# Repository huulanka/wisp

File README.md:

# Wisp

Wisp is an open-source, self-hosted ESP32 room climate monitor. No cloud —
it publishes readings over MQTT into your own Home Assistant instance, which
exposes them to Apple HomeKit.

It tracks:

- **CO2** — SCD41
- **VOC / NOx (air quality)** — SGP41
- **Temperature & humidity** — SCD41, cross-checked against BME280
- **Barometric pressure** — BME280 (also compensates the SCD41's CO2 reading)
- **Ambient light** — BH1750

All hardware, firmware, and infrastructure needed to build and run one live
in this single repo.

## Repo structure

| Path | What's there | Status |
|---|---|---|
| [`/hardware`](hardware/) | KiCad project for the PCB — schematic, layout, Gerbers, BOM/CPL. ESP32-S3-WROOM-1 module, I2C sensors, USB-C only, 4-layer board. | Schematic and PCB routed, DRC clean, fab outputs exported. |
| `/firmware` | ESP-IDF firmware in Rust (`esp-idf-svc`), publishing sensor data over MQTT with OTA updates. | Not started. Design: [`docs/firmware-architecture.md`](docs/firmware-architecture.md). |
| `/infra` | Docker Compose: Mosquitto (MQTT, TLS, ACLs), a self-hosted OTA server, and Home Assistant bridging MQTT into HomeKit. | Not started. Design: [`docs/infra-architecture.md`](docs/infra-architecture.md). |
| [`/docs`](docs/) | Design concept, sensor rationale, expandability notes. | [`concept.md`](docs/concept.md), [`hardware-expandability.md`](docs/hardware-expandability.md). |

## Why these sensors

The SGP41 replaces the more common BME680: the BME680's gas reading only
becomes useful through Bosch's closed-source BSEC library, which doesn't sit
well with an MIT-licensed firmware. Sensirion's Gas Index Algorithm
(BSD-3-Clause) does the same job openly. Dropping the BME680 would also drop
barometric pressure, so the BME280 sits alongside the SGP41 for that —
and because the SCD41 needs ambient pressure to compensate its own CO2
reading, that pressure reading isn't a bonus, it feeds the primary
measurement.

Temperature and humidity are read from the SCD41; the BME280's readings are
kept as an independent cross-check rather than the source of truth, so
firmware can notice a failing sensor.

Full rationale: [`docs/concept.md`](docs/concept.md).

## MQTT topic structure

```
home/climate/<room>/{co2,temperature,humidity,voc,nox,pressure,lux}
```

First room: living room.

## Licensing

Each subfolder is licensed separately, matching its content type:

- [`/hardware`](hardware/LICENSE) → CERN-OHL-S v2
- `/firmware` → MIT
- `/docs` → CC-BY-4.0

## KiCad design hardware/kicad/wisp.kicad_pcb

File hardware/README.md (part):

# hardware

KiCad project for the Wisp board. See `/hardware/kicad` for schematic/PCB
source, `/hardware/scripts` for the generators that produce them, and
`/hardware/fab` for exported Gerbers/drill/BOM/CPL.

Board: **60 x 80 mm, 4 layers**, single-sided assembly (all parts on F.Cu).

## The design is generated, not hand-drawn

This is the most important thing to know before touching anything here.

| File | Role |
|---|---|
| `scripts/wisp_netlist.py` | **The design.** Every part, value, footprint, MPN and net. |
| `scripts/wisp_floorplan.py` | **The placement.** Fixed positions for the parts whose location is a decision; anchors for everything else. Also the board outline. |
| `scripts/gen_schematic.py` | builds `wisp.kicad_sch` |
| `scripts/gen_pcb.py` | builds `wisp.kicad_pcb`, in stages |

Edit the data, re-run the generators. **Do not hand-edit `wisp.kicad_sch`** —
it is overwritten. Rev A's schematic was produced by a throwaway script that
was never committed, which is why by Rev B nobody could reconstruct how it had
been built. That is the problem these two files exist to prevent.

```
python3 hardware/scripts/gen_schematic.py

KI=/Applications/KiCad/KiCad.app/Contents/Frameworks/Python.framework/Versions/Current/bin/python3
for s in strip outline build bond fill; do $KI hardware/scripts/gen_pcb.py $s; done
# ... route (see below) ...
for s in close join polish silk fill; do $KI hardware/scripts/gen_pcb.py $s; done
```

The PCB generator runs as **separate processes per stage on purpose**. pcbnew's
SWIG bindings stop resolving types for the rest of the interpreter once
anything has been `Remove()`d from the board — zones come back as raw
`SwigPyObject`, `GetTracks()` stops being iterable, `FootprintLoad()` breaks,
and some combinations segfault outright. Every stage therefore does its reads
first, its deletions last, and hands off through the file.

### Stages

| Stage | Does |
|---|---|
| `strip` | resets the antenna keepout and the zone outlines, then deletes all copper and footprints |
| `outline` | rewrites Edge.Cuts from `wisp_floorplan.OUTLINE` (plain text — it both deletes and creates) |
| `build` | places all 91 footprints and assigns every net from the schematic netlist |
| `bond` | gives each SMD power pad its own via to its plane, plus a GND stitching grid |
| `fill` | refills all five zones |
| `close` | deletes vias/tracks the router left dangling; run until it reports none |
| `join` | closes any connection the router left open, with a collision-checked A* |
| `polish` | widens anything below the 0.15mm minimum track width |
| `silk` | makes the silkscreen manufacturable (see below) |

## Validating the design

```
kicad-cli sch erc --severity-all --format json --output erc.json hardware/kicad/wisp.kicad_sch
kicad-cli pcb drc --severity-all --format json --output drc.json hardware/kicad/wisp.kicad_pcb
```

Run these against the project directory, not against a copy of
`wisp.kicad_pcb` somewhere else: `kicad-cli` only picks up
`wisp.kicad_dru` and `wisp.kicad_pro` by path, and the project file is where
the design rules live.

`gen_schematic.py` additionally refuses to emit anything unless every net
references a pin that exists, every footprint file resolves, and **every pin
of every part is claimed by exactly one net or explicitly listed in
`NO_CONNECT`**. That last check is what stops a forgotten pin from quietly
becoming an unrouted net three stages later.

## Stackup

| Layer | Use |
|---|---|
| **F.Cu** | components + signal routing, GND fill in the gaps |
| **In1.Cu** (`GND`) | **solid, uncut ground plane** |
| **In2.Cu** (`PWR`) | **solid +3V3 plane** |
| **B.Cu** | signal routing, GND fill in the gaps |

Nothing is ever routed on the two inner layers — they are planes only. The
Specctra DSN handed to the autorouter declares them `(type power)` so the
router cannot cut them; if you re-export the DSN, re-apply that patch, since
KiCad exports all four layers as `(type signal)` by default.

## Power distribution

Every **surface-mount** `+3V3`/`GND` pad gets its own short stub and via
straight down to the plane that owns that net, placed just off the pad by a
collision-checked search. Power connectivity never depends on a pour reaching
a pad. Rev A's long-running "unconnected pour island" findings were all that
failure mode; with a via per pad, a power pad can only be unconnected if its
via is missing, which DRC reports directly.

Two deliberate exceptions:

- **Plated through-hole pads are not bonded.** A PTH pad already spans
  F.Cu..B.Cu and meets its plane on the way through. Adding a via beside it
  buys nothing and puts a second drill 0.4mm from the first — that was the
  source of most hole-to-hole violations and of two dangling `+3V3` vias
  during the Rev B bring-up.
- **Large exposed pads get a via array inside the pad** (the SCD41's 4.8mm
  thermal pad, the module's 3.9mm one). A stub to a via outside them cannot
  even be searched for, because every candidate within 3mm of the pad centre
  is still on the pad. This is what a thermal pad wants anyway.

Both the via *and the stub track leading to it* are collision-checked.
Checking only the via lets the stub cut straight across whatever pad lies
between — 61 GND/+3V3 shorts on the first attempt.

## Floorplan

Placement is by function, not by arithmetic.

```
 y 0.0-7.5    antenna keepout, all four copper layers, x 8..52
 y 0.75-26.3  U3 ESP32-S3-WROOM-1, antenna flush with the top edge
 y 8-30       left: EN/IO0 support, reset+boot buttons, status LED
              right: J2/J3 headers on the right edge
 y 30-46      USB-C (left edge) -> U8 ESD -> F1 -> U2 buck -> L1
 y 43-48      test point grid, 4.0mm pitch
 y 48-62      left: small headers; right: J4/J9; buzzer
 y 62-80      sensor tab, milled free on three sides
```

Rules this enforces:

- **Decoupling sits next to the pin it serves.** `wisp_floorplan.ANCHOR` names
  the pad each passive belongs to and `gen_pcb.py` runs a collision-checked
  spiral search outward from it. The ESP32's 100nF and 10uF, the SCD41's
  100nF, and the SGP41's RC element all land within a few millimetres of their
  pin. Rev A had all of its decoupling on the *opposite* copper layer, 8-20mm
  away, where above a few MHz it does essentially nothing.
- **A part may not cross the milled slot to reach its pin.** The slot splits
  the board into exactly two regions, and the placer requires a part to land
  in the same one as its anchor pad. Without that check the SCD41's bulk
  capacitor was placed 10mm away with a slot in between.
- **Fixed placements are checked against each other.** Pin headers are
  anchored at pin 1, not at their centre, so a 1x08 header extends ~20mm
  *downwards* from its coordinate; spacing them by centre is how J5/J7 and
  J9/MH4 first ended up overlapping.
- **All 91 parts are on the front.** Single-sided assembly is cheaper, and it
  keeps the inner ground plane the only thing between the two routing layers.

## RF: antenna placement

`U3` sits at the top board edge with its antenna end pointing off-board, so
the required clearance is mostly free air rather than reserved board area. A
rule area over `x 8..52, y 0..7.5` forbids tracks, vias, pads and zone fill on
**all four copper layers**.

Rev A cleared only the module's own width (x 18..42), which left GND pour
flush with the antenna on both sides. This clears ~9mm either side. It stops
short of the board corners so the M3 mounting holes still have somewhere to
live — the keepout forbids pads, and a mounting hole is a pad.

### The module footprint is project-local, and why

`wisp:ESP32-S3-WROOM-1` is a copy of the stock KiCad footprint with two
changes:

1. **The courtyard is trimmed to the module body** (x -9.75..9.75,
   y -12.75..13.45). The stock courtyard is **48 x 41mm**: it applies
   Espressif's 15mm antenna clearance symmetrically around the whole module
   instead of only off the antenna end. Left alone it swallows a third of a
   60x80mm board, blocks every nearby placement, and produces
   courtyard-overlap DRC errors against parts nowhere near the module. Rev A
   hit exactly this with the WROOM-32.
2. **Its built-in antenna keepout zone is removed**, so the board carries one
   deliberate antenna rule area instead of two overlapping ones with different
   extents.

## Thermal isolation of the sensors

SCD41 (`U4`), SGP41 (`U5`), BH1750 (`U6`) and BME280 (`U7`) sit on a tab at
the bottom of the board, x 19.5-49, y 62-80, cut free by a 1.5mm milled slot
on three sides and joined to the main board through a 9mm neck. This is
Sensirion's and Bosch's own recommendation: without it the parts report PCB
temperature rather than room temperature, which for a room climate monitor
defeats the primary function.

The tab is larger than Rev A's 25 x 16.5mm. The SCD41 alone fills 40% of that,
leaving nowhere to put its own decoupling — which is exactly what went wrong
the first time. At 29.5 x 18mm every sensor keeps its decoupling on its own
side of the slot.

The SGP41 is placed at the far end of the tab from the SCD41: it runs a
hotplate, and the SCD41 is the sensor whose temperature reading has to stay
honest.

**Known tradeoff, deliberate:** the GND and +3V3 planes still run through the
neck, so the isolation comes from slot geometry and distance rather than from
a copper break. Narrowing the planes at the neck would improve it further and
remains a reasonable future refinement.

## Routing

Signals are routed with Freerouting (headless, `--gui.enabled=false -mt 1`;
multi-threaded optimisation is flagged by Freerouting itself as producing
clearance violations). The DSN is exported with `pcbnew.ExportSpecctraDSN` —
note that `kicad-cli pcb export` has no `specctra-dsn` subcommand — then
patched so the inner layers are `(type power)`.

Afterwards, `close` removes anything the router left dangling and `join`
closes any remaining open connection with a collision-checked A* over
F.Cu/B.Cu with via transitions. `join` reads the DRC report to find what is
open and rasterises the **whole** target net as its goal; aiming at a single
reported coordinate is fragile, because a track's `GetPosition()` is one end
of it rather than the nearest point.

**Minimum track width is 0.15mm.** The escapes under the fine-pitch sensors
genuinely need it, and it is comfortably inside JLCPCB's 4-layer capability
(0.127mm). Rev A instead routed at 0.25mm clearance and widened the router's
0.15mm stubs back to 0.20mm afterwards; doing that here created clearance
violations against neighbouring pads, and re-routing at 0.25mm made the router
thrash without converging.

**If a net comes back unroutable, look at the test points first.** They sit in
the busiest part of the board, and at Rev A's 3.2mm pitch the router boxed one
in completely — a net that no amount of post-processing can reach, because the
pad has no escape lane in any direction. They are at 4.0mm pitch now.

### J1 (USB-C)

The receptacle brings D+ out on pads A6/B6 and D- on A7/B7, interleaved down
the column as **B6, A7, A6, B7** at 0.5mm pitch, so connecting each pair needs
exactly one layer crossing and a 0.6mm via needs ~1.2mm of vertical room. On
Rev A this required a hand-placed fanout before autorouting.

On Rev B the pair runs J1 -> U8 (USBLC6 ESD array) -> U3 rather than J1 -> a
UART bridge, and U8 is placed to give the crossing room, so the autorouter
solves it unaided. If you re-place J1 or U8 and D- comes back unroutable, this
is why.

## Silkscreen

At 91 parts on 60x80mm a footprint's own silk outline routinely lands on the
neighbouring part's pads. The `silk` stage:

- moves every footprint silk **graphic** to F.Fab, where it still appears in
  the assembly drawing;
- **auto-places the reference designators** with a collision-checked search
  against pads, board edge and each other, largest parts first, and demotes
  only the ones with nowhere to go;
- moves **Value** to F.Fab;
- and hides the custom metadata fields.

That last one matters more than it sounds. `MPN`, `Manufacturer`, `Rating` and
`LCSC` are created on **F.SilkS by default and parked at the footprint
origin**, stacked on top of each other and on the pads — 422 text items nobody
ever intended to print. They are not returned by `GraphicalItems()`, so they
are invisible to every other pass, and they were the entire source of ~440
silkscreen DRC violations. If silkscreen violations reappear after adding a
field, this is the first place to look.

## Known ERC warnings (accepted, not bugs)

**`Pins of type Bidirectional and Power output are connected`** (U7 pin 5 /
SDO tied to GND)

`U7` (BME280) pin 5 (SDO) is intentionally strapped to GND to select I2C
address `0x76`. The symbol marks SDO `Bidirectional`, so ERC flags any
bidirectional pin wired to a power net. Either address strap produces this;
it cannot be avoided while the address is fixed in hardware.

Rev A's two `lib_symbol_mismatch` warnings are gone: the generator embeds
symbols straight from the installed library, so a cached copy cannot drift
from it.

## Known DRC findings

None. `kicad-cli pcb drc --severity-all` is clean: 0 violations, 0 unconnected
items, 0 schematic-parity errors.

This is no longer a low bar: `wisp.kicad_dru` used to carry no rules, and the
board's own `min_silk_clearance` / `solder_mask_to_copper_clearance` were both
0mm, so KiCad's DRC could not have caught a real fab-capability problem even
if one existed. A JLCPCB DFM report against an earlier build of this board
found real ones — 0.15mm silk-line width flagged, silkscreen text on top of
vias, negative silk/pad clearance — none of which local DRC saw, because
nothing was checking for it. Design rules in `wisp.kicad_pro` now match
JLCPCB's published capability (`min_silk_clearance` 0.15mm,
`solder_mask_to_copper_clearance` 0.1mm, `min_hole_clearance` 0.3mm) instead
of the KiCad defaults, and DRC is clean against those.

The root cause of the silkscreen findings was in `gen_pcb.py`'s `silk` stage,
not just the missing rule: reference-designator placement estimated each
label's width from a `0.62mm/character` formula instead of asking KiCad for
the real rendered bounding box, and undershot it by up to 0.48mm — enough
that designators the search believed were clear were actually touching
neighbouring pads and vias. It also never considered vias as obstacles at
all. Both are fixed: the search now queries `GetBoundingBox()` on the actual
text object, and vias are indexed alongside pads.

Three design rules were deliberately changed from Rev A/B, all recorded in
`wisp.kicad_pro`:

- `min_track_width` 0.20 -> **0.15mm** — see Routing above.
- `min_resolved_spokes` 2 -> **1** — a handful of GND pads can only get one
  thermal spoke past their neighbours. One spoke is a valid connection, and
  every affected pad is a power pad that also carries its own plane via, so
  the spoke is a secondary path in any case.
- `min_hole_clearance` 0.25 -> **0.3mm** — JLCPCB's stated absolute minimum is
  0.28mm; 0.25 was below it even though nothing on the board was actually
  that tight.

Two things the DFM report flags that are **not** being changed, both reviewed
and accepted rather than silently ignored:

- **Every via's annular ring is 0.15mm** (0.6mm pad / 0.3mm drill), which
  JLCPCB's own DFM tool marks as a Warning because it sits exactly at their
  stated *absolute minimum* rather than their *recommended* 0.20mm. Widening
  every via on this already-dense 60x80mm/91-part board would mean re-routing
  under a tighter budget for a purely precautionary margin; treated the same
  way as the `min_track_width` and `min_resolved_spokes` exceptions above.
- **J1's four shield-ground pads are 0.6mm oval plated slots**, flagged by
  JLCPCB as a slot-width Danger. This geometry comes from KiCad's own stock
  `Connector_USB:USB_C_Receptacle_HRO_TYPE-C-31-M-12` footprint (the part
  actually specified: HRO TYPE-C-31-M-12, LCSC C165948), not from anything
  wisp-specific, and the same footprint is in wide use on JLCPCB-fabricated
  boards. Not changed here since fixing it means swapping the connector
  itself; worth a manual check with JLCPCB before ordering if it matters for
  your run.

## Fab outputs

`hardware/fab/gerbers/` contains only the layers a fab actually needs — the
four copper layers, paste, silkscreen, mask and the board profile, plus
separate PTH/NPTH Excellon drill files and their maps.

Check `wisp-job.gbrjob` after any re-export: it must report `LayerNumber: 4`
with `Copper,L1,Top` / `Copper,L2,Inr` / `Copper,L3,Inr` / `Copper,L4,Bot`.
That file, not the filename extension, is what states the stackup order.

## Before ordering

**`wisp:BH1750FVI-TR_WSOF6` is now verified.** ROHM's mechanical drawing
(BH1750FVI Technical Note No.11046EDT01 Rev.D, p.14 "Package Outlines") turned
out to be reachable after all; the land pattern was rebuilt from its figures
(body 1.6 x 2.6mm, 0.5mm pitch, 0.22mm lead width, 0.27mm lead foot) and
cross-checked against the LCSC C78960 listing's own generated footprint,
which agrees on pitch and pad size once its axes are rotated into this
footprint's convention. Pin 7 is the exposed centre pad; the datasheet (p.16,
"Cautions on use" #10) says explicitly not to solder or electrically connect
it, so it is copper-only with no paste and no net, for mechanical registration
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
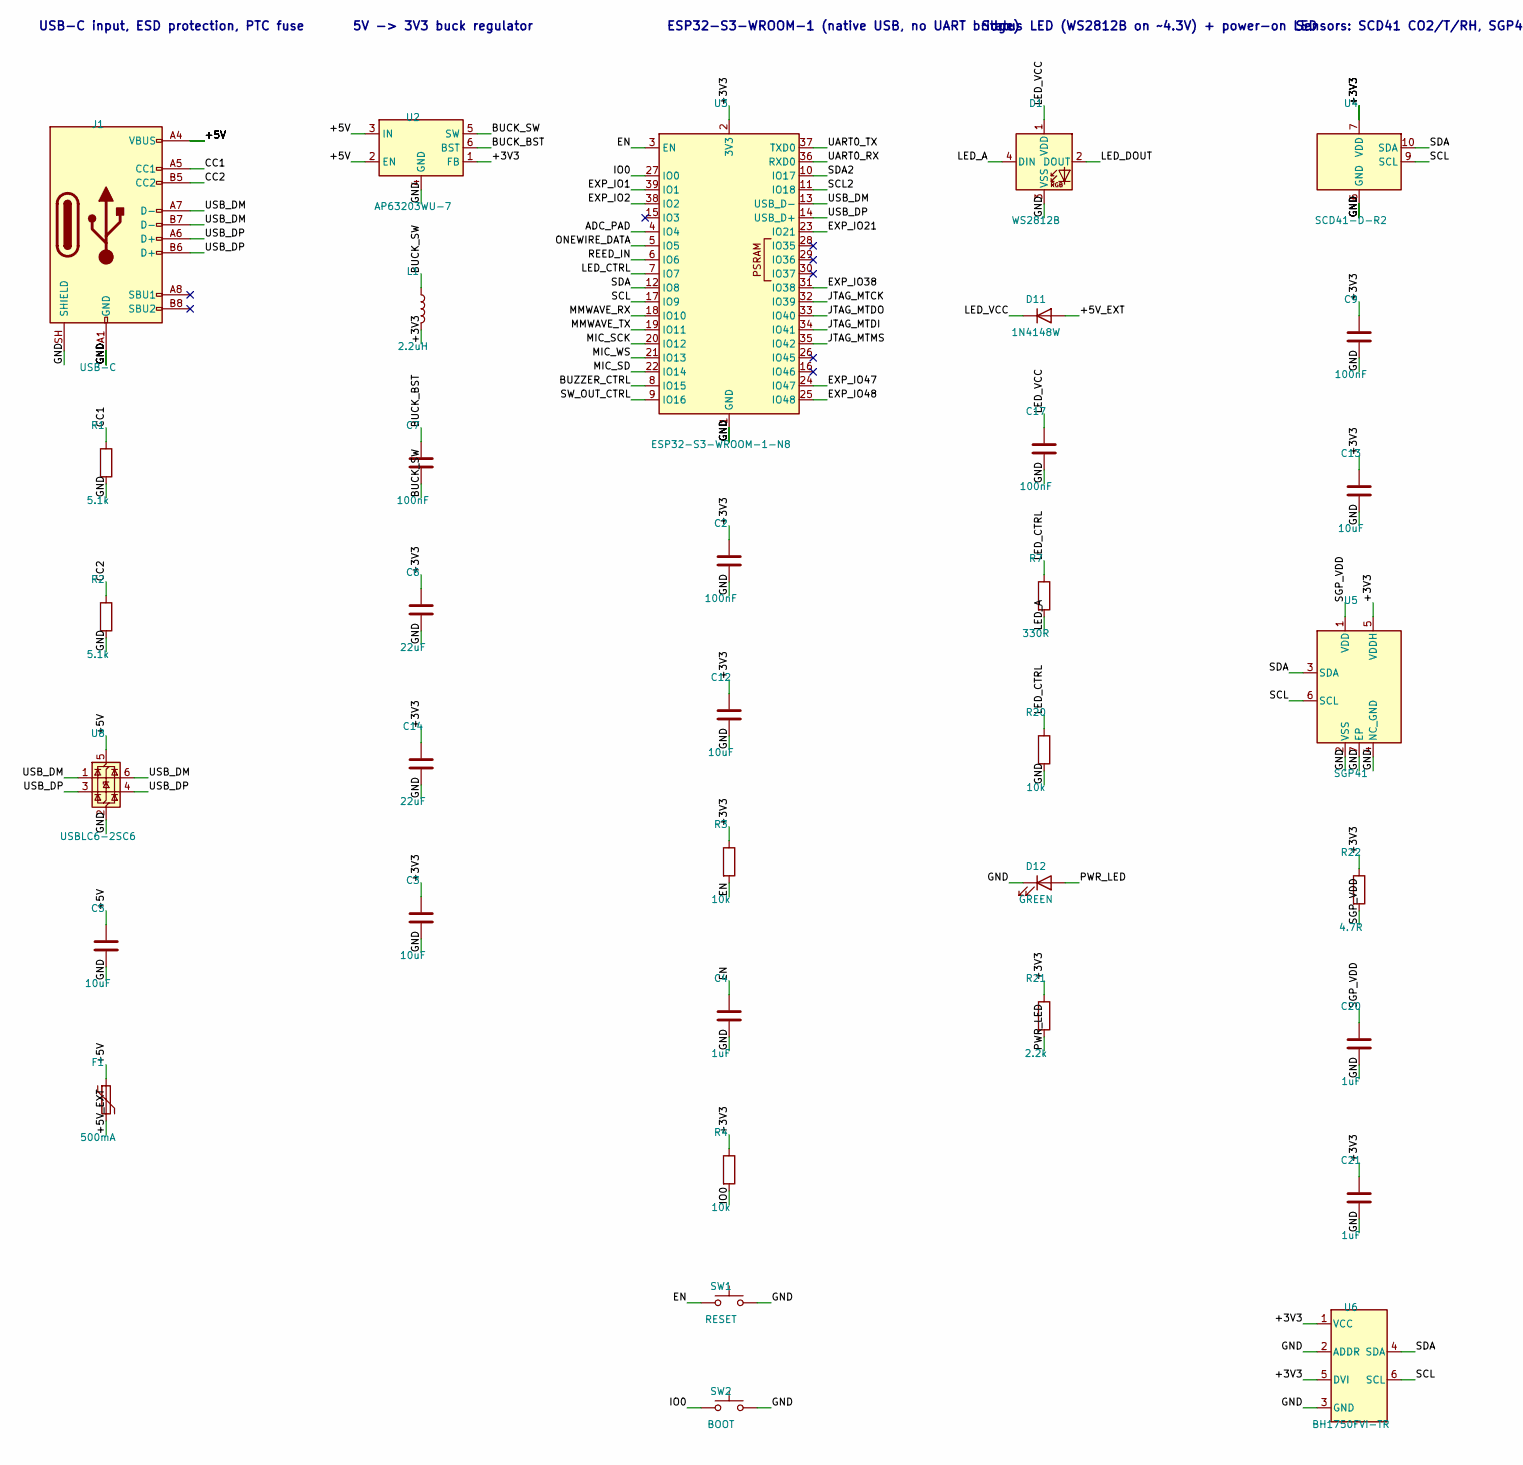
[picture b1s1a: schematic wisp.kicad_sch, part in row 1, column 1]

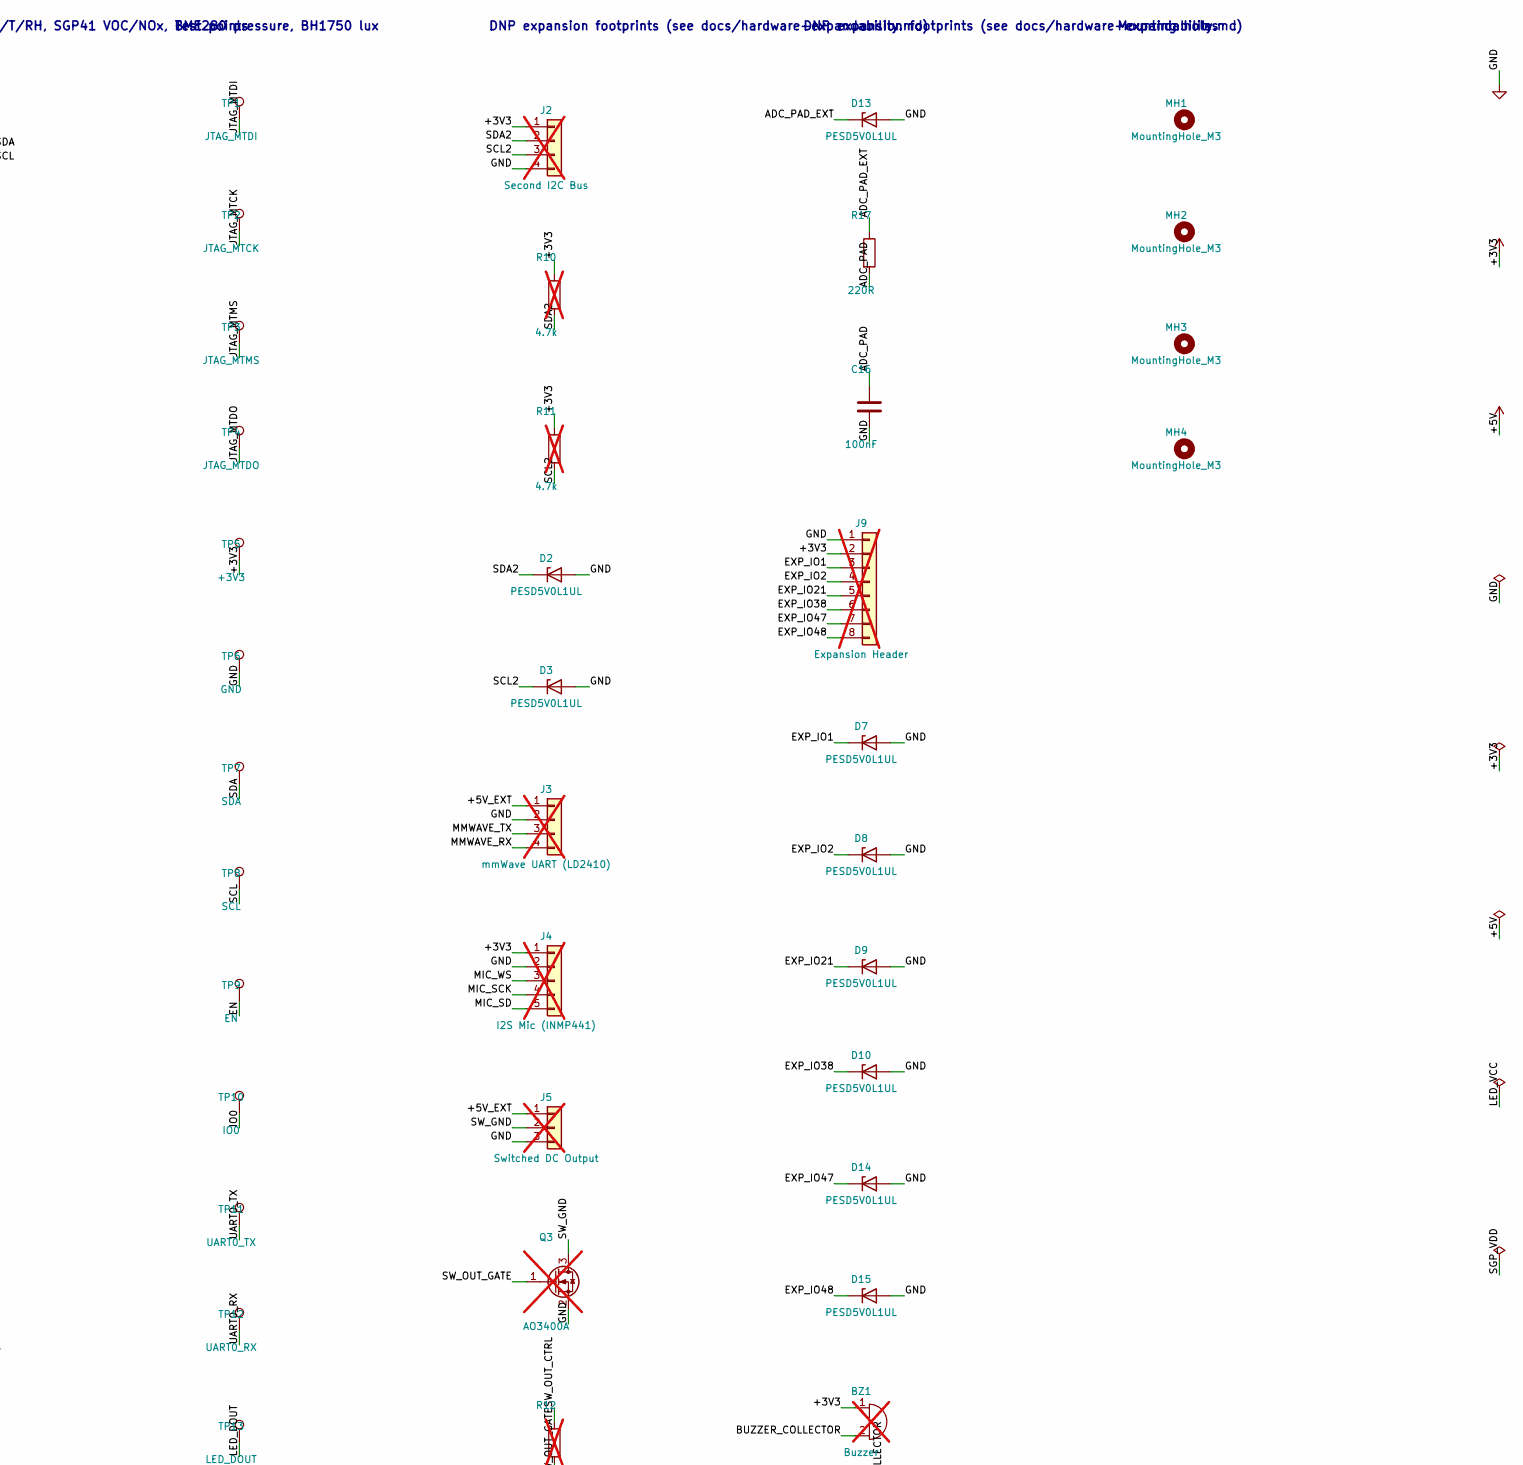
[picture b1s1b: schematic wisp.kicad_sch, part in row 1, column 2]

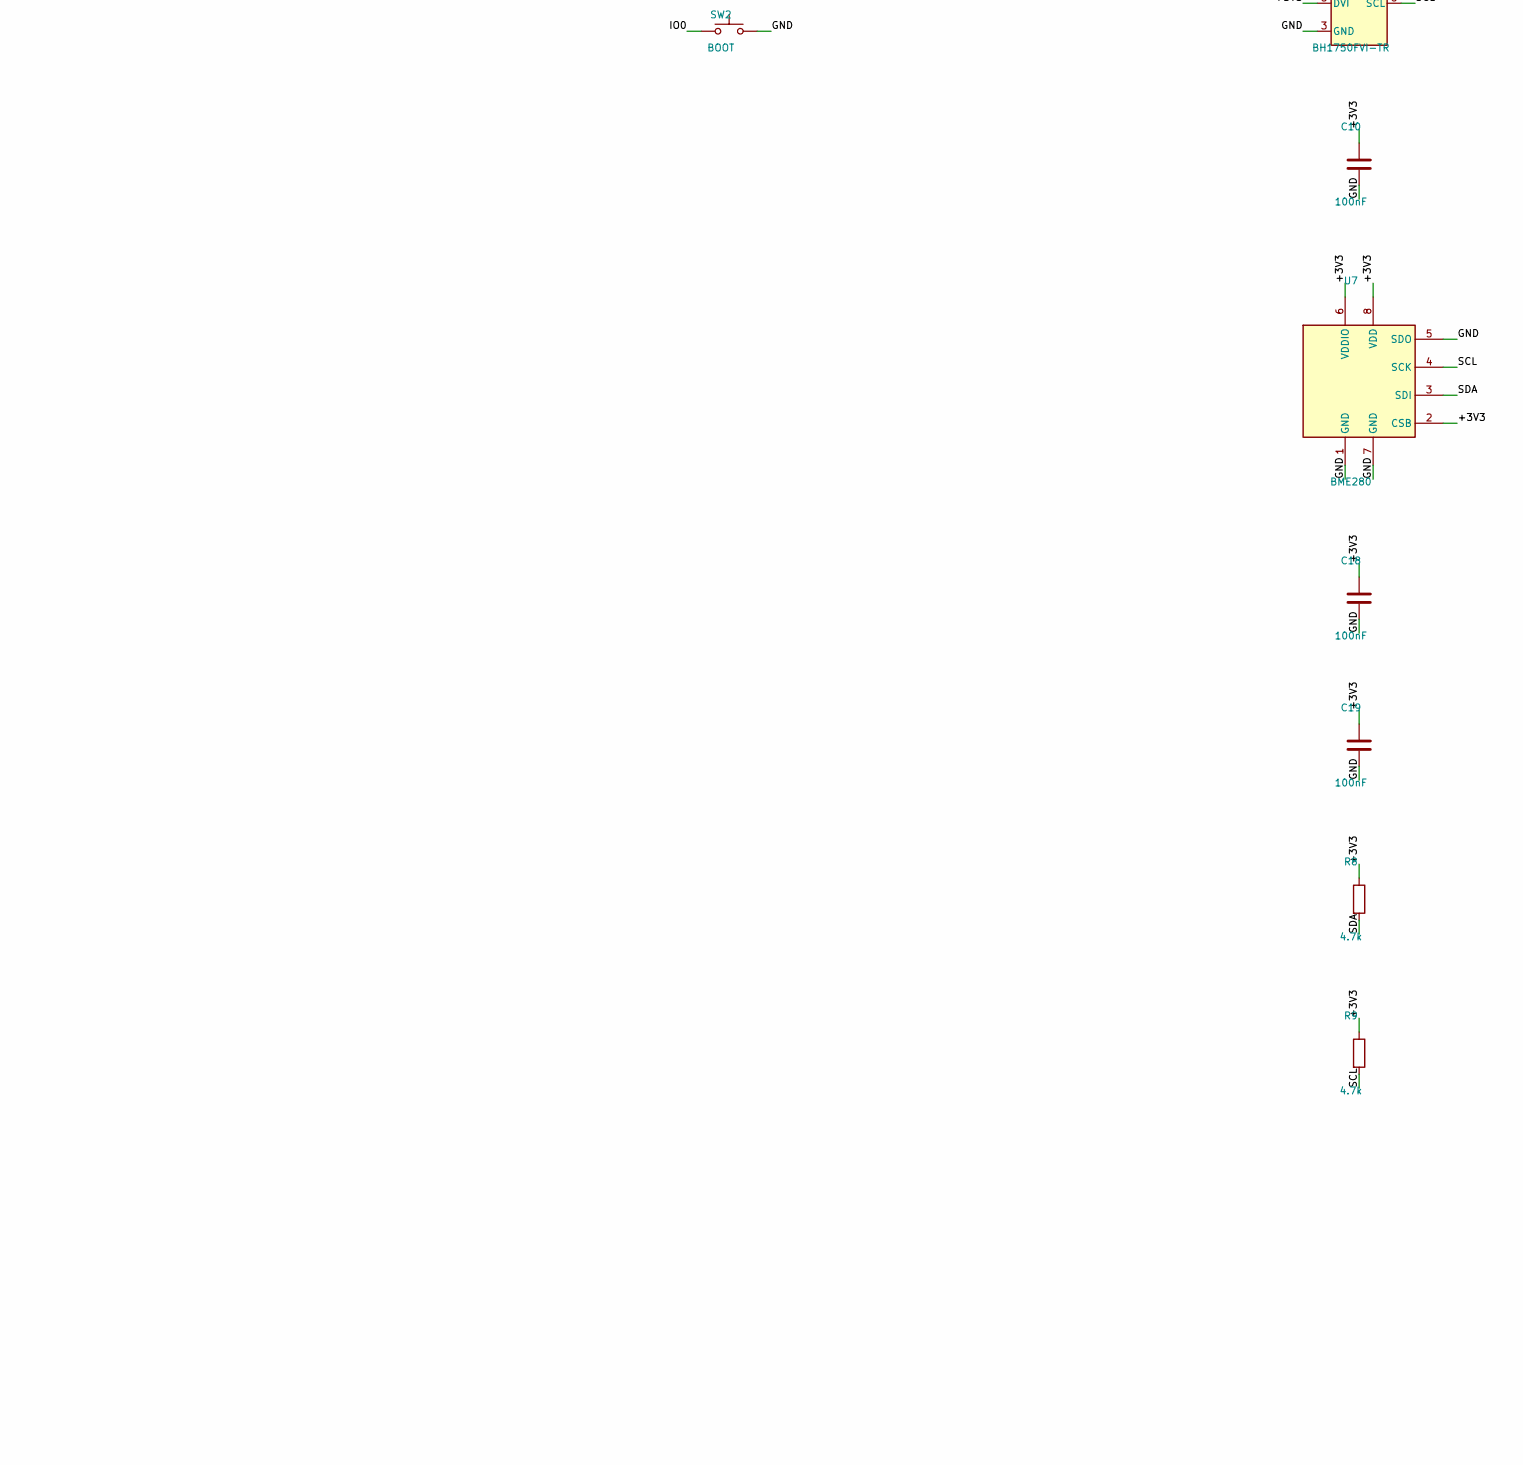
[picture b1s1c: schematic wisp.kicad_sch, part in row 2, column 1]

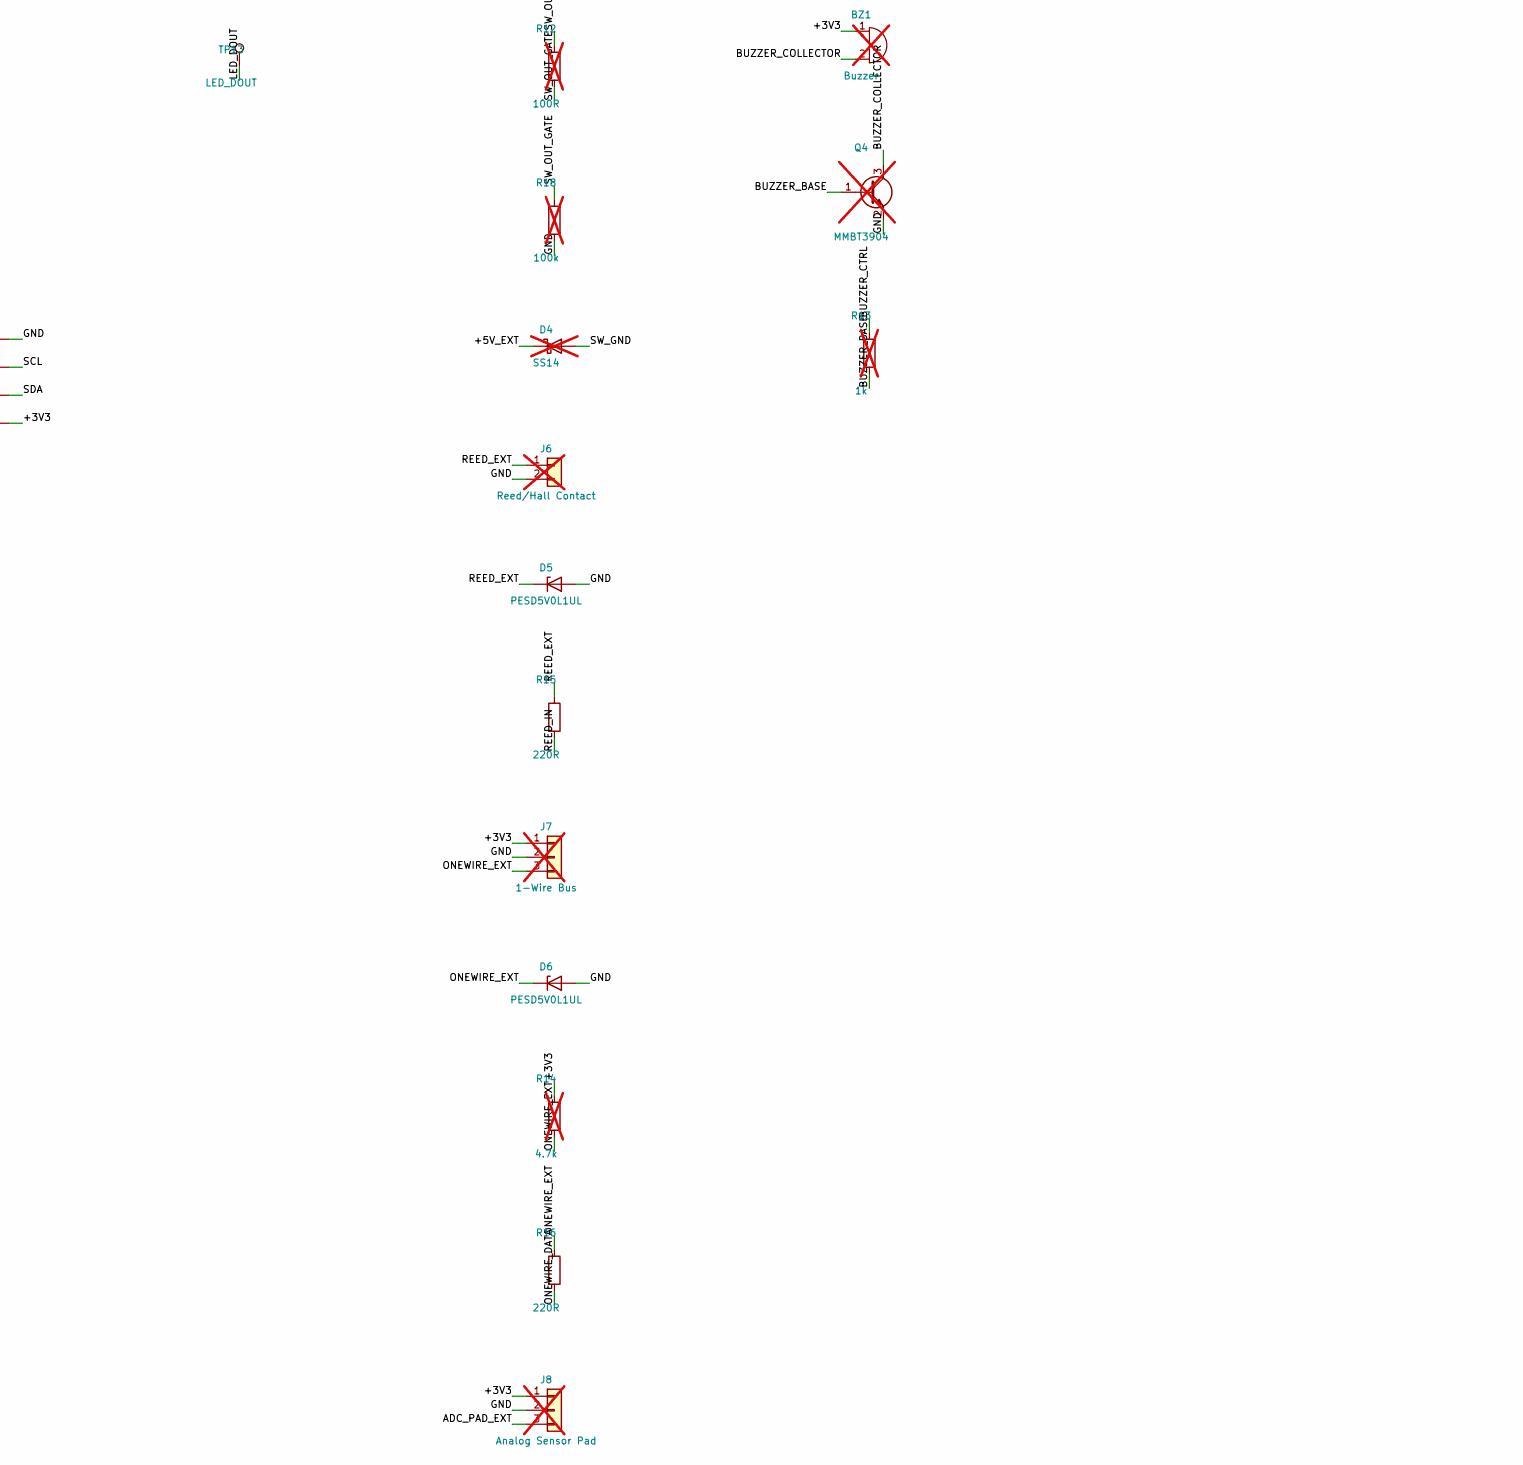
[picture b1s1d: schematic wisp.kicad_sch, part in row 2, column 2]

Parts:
BZ1: Buzzer; Buzzer_CUI_CPT-9019S-SMT; Rating piezo transducer, external drive; MPN CPT-9019S-SMT; LCSC C95163; not fitted
C2, C7, C9, C10, C17, C18, C19: 100nF; C_0805_2012Metric; Rating 50V X7R; MPN CL21B104KBCNNNC; LCSC C1711
C3, C12, C13: 10uF; C_0805_2012Metric; Rating 16V X5R; MPN CL21A106KOQNNNE; LCSC C1713
C4, C20, C21: 1uF; C_0805_2012Metric; Rating 50V X7R; MPN CL21B105KBFNNNE; LCSC C28323
C5: 10uF; C_0805_2012Metric; Rating 25V X5R; MPN CL21A106KOQNNNE; LCSC C1713
C6, C14: 22uF; C_0805_2012Metric; Rating 16V X5R; MPN CL21A226MOQNNNE; LCSC C98190
C16: 100nF; C_0805_2012Metric; Rating 50V X7R, ADC filter; MPN CL21B104KBCNNNC; LCSC C1711
D1: WS2812B; LED_WS2812B_PLCC4_5.0x5.0mm_P3.2mm; Rating VDD 3.5-5.3V; MPN WS2812B-B/T; LCSC C2761795
D2, D3, D5, D6, D7, D8, D9, D10, D13, D14, D15: PESD5V0L1UL; D_SOD-882; MPN PESD5V0L1UL; LCSC C552556
D4: SS14; D_SMA; Rating Schottky 1A/40V, flyback for the switch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; MPN SS14; LCSC C2480; not fitted
D11: 1N4148W; D_SOD-123; Rating drops +5V_EXT to ~4.3V for D1; MPN 1N4148W-7-F; LCSC C83528
D12: GREEN; LED_0805_2012Metric; Rating green, power-on indicator; MPN KT-0805G; LCSC C2297
F1: 500mA; Fuse_1812_4532Metric; Rating PTC, 500mA hold, 6V; MPN MF-MSMF050-2; LCSC C17313
J1: USB-C; USB_C_Receptacle_HRO_TYPE-C-31-M-12; MPN TYPE-C-31-M-12; LCSC C165948
J2: Second I2C Bus; PinHeader_1x04_P2.54mm_Vertical; not fitted
J3: mmWave UART (LD2410); PinHeader_1x04_P2.54mm_Vertical; not fitted
J4: I2S Mic (INMP441); PinHeader_1x05_P2.54mm_Vertical; not fitted
J5: Switched DC Output; PinHeader_1x03_P2.54mm_Vertical; not fitted
J6: Reed/Hall Contact; PinHeader_1x02_P2.54mm_Vertical; not fitted
J7: 1-Wire Bus; PinHeader_1x03_P2.54mm_Vertical; not fitted
J8: Analog Sensor Pad; PinHeader_1x03_P2.54mm_Vertical; not fitted
J9: Expansion Header; PinHeader_1x08_P2.54mm_Vertical; not fitted
L1: 2.2uH; L_1210_3225Metric; Rating Isat >= 1.5A, DCR < 100mOhm; MPN SRN3015-2R2M; LCSC C2041716
MH1, MH2, MH3, MH4: MountingHole_M3; MountingHole_3.2mm_M3
Q3: AO3400A; SOT-23; Rating logic-level N-FET, 5.7A, Vgs(th) < 1.4V; MPN AO3400A; LCSC C20917; not fitted
Q4: MMBT3904; SOT-23; MPN MMBT3904; LCSC C81464; not fitted
R1, R2: 5.1k; R_0805_2012Metric; Rating 1%, 1/8W; MPN RC0805FR-075K1L; LCSC C84375
R3, R4, R20: 10k; R_0805_2012Metric; Rating 1%, 1/8W; MPN RC0805FR-0710KL; LCSC C84376
R7: 330R; R_0805_2012Metric; Rating 1%, 1/8W; MPN RC0805FR-07330RL; LCSC C105878
R8, R9: 4.7k; R_0805_2012Metric; Rating 1%, I2C pull-up; MPN RC0805FR-074K7L; LCSC C60816
R10, R11: 4.7k; R_0805_2012Metric; Rating 1%; MPN RC0805FR-074K7L; LCSC C60816; not fitted
R12: 100R; R_0805_2012Metric; Rating 1%, gate series; MPN RC0805FR-07100RL; LCSC C105577; not fitted
R13: 1k; R_0805_2012Metric; Rating 1%, base series; MPN RC0805FR-071KL; LCSC C95781; not fitted
R14: 4.7k; R_0805_2012Metric; Rating 1%, 1-Wire pull-up; MPN RC0805FR-074K7L; LCSC C60816; not fitted
R15, R16, R17: 220R; R_0805_2012Metric; Rating 1%, ESD series; MPN RC0805FR-07220RL; LCSC C114519
R18: 100k; R_0805_2012Metric; Rating 1%, gate pull-down; MPN RC0805FR-07100KL; LCSC C96346; not fitted
R21: 2.2k; R_0805_2012Metric; Rating 1%, 1/8W; MPN RC0805FR-072K2L; LCSC C114561
R22: 4.7R; R_0805_2012Metric; Rating 1%, SGP41 VDD RC element; MPN RC0805FR-074R7L; LCSC C137513
SW1: RESET; SW_SPST_PTS810; MPN PTS810 SJM 250 SMTR LFS; LCSC C116501
SW2: BOOT; SW_SPST_PTS810; MPN PTS810 SJM 250 SMTR LFS; LCSC C116501
TP1: JTAG_MTDI; TestPoint_Pad_1.5x1.5mm
TP2: JTAG_MTCK; TestPoint_Pad_1.5x1.5mm
TP3: JTAG_MTMS; TestPoint_Pad_1.5x1.5mm
TP4: JTAG_MTDO; TestPoint_Pad_1.5x1.5mm
TP5: +3V3; TestPoint_Pad_1.5x1.5mm
TP6: GND; TestPoint_Pad_1.5x1.5mm
TP7: SDA; TestPoint_Pad_1.5x1.5mm
TP8: SCL; TestPoint_Pad_1.5x1.5mm
TP9: EN; TestPoint_Pad_1.5x1.5mm
TP10: IO0; TestPoint_Pad_1.5x1.5mm
TP11: UART0_TX; TestPoint_Pad_1.5x1.5mm
TP12: UART0_RX; TestPoint_Pad_1.5x1.5mm
TP13: LED_DOUT; TestPoint_Pad_1.5x1.5mm
U2: AP63203WU-7; TSOT-23-6; Rating 2A sync buck, fixed 3.3V; MPN AP63203WU-7; LCSC C780769
U3: ESP32-S3-WROOM-1-N8; ESP32-S3-WROOM-1; Rating 8MB flash, no PSRAM; MPN ESP32-S3-WROOM-1-N8; LCSC C2913198
U4: SCD41-D-R2; Sensirion_SCD4x-1EP_10.1x10.1mm_P1.25mm_EP4.8x4.8mm; Rating CO2/T/RH, I2C 0x62; MPN SCD41-D-R2
U5: SGP41; Sensirion_DFN-6-1EP_2.44x2.44mm_P0.8mm_EP1.25x1.7mm; Rating VOC/NOx, I2C 0x59; MPN SGP41-D-R4
U6: BH1750FVI-TR; BH1750FVI-TR_WSOF6; Rating lux, I2C 0x23; MPN BH1750FVI-TR; LCSC C78960
U7: BME280; Bosch_LGA-8_2.5x2.5mm_P0.65mm_ClockwisePinNumbering; Rating pressure/T/RH, I2C 0x76; MPN BME280; LCSC C92489
U8: USBLC6-2SC6; SOT-23-6; Rating ESD array, D+/D-/VBUS; MPN USBLC6-2SC6; LCSC C7519

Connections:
+3V3: BZ1.1 (+), C2.1, C3.1, C6.1, C9.1, C10.1, C12.1, C13.1, C14.1, C18.1, C19.1, C21.1, J2.1, J4.1, J7.1, J8.1, J9.2, L1.2, R3.1, R4.1, R8.1, R9.1, R10.1, R11.1, R14.1, R21.1, R22.1, TP5.1, U2.1 (FB), U3.2 (3V3), U4.7 (VDD), U4.19 (VDD), U5.5 (VDDH), U6.1 (VCC), U6.5 (DVI), U7.2 (CSB), U7.6 (VDDIO), U7.8 (VDD)
+5V: C5.1, F1.1, J1.A4 (VBUS), J1.A9 (VBUS), J1.B4 (VBUS), J1.B9 (VBUS), U2.2 (EN), U2.3 (IN), U8.5 (VBUS)
/+5V_EXT: D4.1 (K), D11.2 (A), F1.2, J3.1, J5.1
/ADC_PAD: C16.1, R17.2, U3.4 (IO4)
/ADC_PAD_EXT: D13.1 (K), J8.3, R17.1
/BUCK_BST: C7.1, U2.6 (BST)
/BUCK_SW: C7.2, L1.1, U2.5 (SW)
/BUZZER_BASE: Q4.1 (B), R13.2
/BUZZER_COLLECTOR: BZ1.2 (-), Q4.3 (C)
/BUZZER_CTRL: R13.1, U3.8 (IO15)
/CC1: J1.A5 (CC1), R1.1
/CC2: J1.B5 (CC2), R2.1
/EN: C4.1, R3.2, SW1.1, TP9.1, U3.3 (EN)
/EXP_IO1: D7.1 (K), J9.3, U3.39 (IO1)
/EXP_IO2: D8.1 (K), J9.4, U3.38 (IO2)
/EXP_IO21: D9.1 (K), J9.5, U3.23 (IO21)
/EXP_IO38: D10.1 (K), J9.6, U3.31 (IO38)
/EXP_IO47: D14.1 (K), J9.7, U3.24 (IO47)
/EXP_IO48: D15.1 (K), J9.8, U3.25 (IO48)
/IO0: R4.2, SW2.1, TP10.1, U3.27 (IO0)
/JTAG_MTCK: TP2.1, U3.32 (IO39)
/JTAG_MTDI: TP1.1, U3.34 (IO41)
/JTAG_MTDO: TP4.1, U3.33 (IO40)
/JTAG_MTMS: TP3.1, U3.35 (IO42)
/LED_A: D1.4 (DIN), R7.2
/LED_CTRL: R7.1, R20.1, U3.7 (IO7)
/LED_DOUT: D1.2 (DOUT), TP13.1
/LED_VCC: C17.1, D1.1 (VDD), D11.1 (K)
/MIC_SCK: J4.4, U3.20 (IO12)
/MIC_SD: J4.5, U3.22 (IO14)
/MIC_WS: J4.3, U3.21 (IO13)
/MMWAVE_RX: J3.4, U3.18 (IO10)
/MMWAVE_TX: J3.3, U3.19 (IO11)
/ONEWIRE_DATA: R16.2, U3.5 (IO5)
/ONEWIRE_EXT: D6.1 (K), J7.3, R14.2, R16.1
/PWR_LED: D12.2 (A), R21.2
/REED_EXT: D5.1 (K), J6.1, R15.1
/REED_IN: R15.2, U3.6 (IO6)
/SCL: R9.2, TP8.1, U3.17 (IO9), U4.9 (SCL), U5.6 (SCL), U6.6 (SCL), U7.4 (SCK)
/SCL2: D3.1 (K), J2.3, R11.2, U3.11 (IO18)
/SDA: R8.2, TP7.1, U3.12 (IO8), U4.10 (SDA), U5.3 (SDA), U6.4 (SDA), U7.3 (SDI)
/SDA2: D2.1 (K), J2.2, R10.2, U3.10 (IO17)
/SGP_VDD: C20.1, R22.2, U5.1 (VDD)
/SW_GND: D4.2 (A), J5.2, Q3.3 (D)
/SW_OUT_CTRL: R12.1, U3.9 (IO16)
/SW_OUT_GATE: Q3.1 (G), R12.2, R18.1
/UART0_RX: TP12.1, U3.36 (RXD0)
/UART0_TX: TP11.1, U3.37 (TXD0)
/USB_DM: J1.A7 (D-), J1.B7 (D-), U3.13 (USB_D-), U8.1 (I/O1), U8.6 (I/O1)
/USB_DP: J1.A6 (D+), J1.B6 (D+), U3.14 (USB_D+), U8.3 (I/O2), U8.4 (I/O2)
GND: C2.2, C3.2, C4.2, C5.2, C6.2, C9.2, C10.2, C12.2, C13.2, C14.2, C16.2, C17.2, C18.2, C19.2, C20.2, C21.2, D1.3 (VSS), D2.2 (A), D3.2 (A), D5.2 (A), D6.2 (A), D7.2 (A), D8.2 (A), D9.2 (A), D10.2 (A), D12.1 (K), D13.2 (A), D14.2 (A), D15.2 (A), J1.A1 (GND), J1.A12 (GND), J1.B1 (GND), J1.B12 (GND), J1.SH (SHIELD), J2.4, J3.2, J4.2, J5.3, J6.2, J7.2, J8.2, J9.1, Q3.2 (S), Q4.2 (E), R1.2, R2.2, R18.2, R20.2, SW1.2, SW2.2, TP6.1, U2.4 (GND), U3.1 (GND), U3.40 (GND), U3.41 (GND), U4.6 (GND), U4.20 (GND), U4.21 (GND), U5.2 (VSS), U5.4 (NC_GND), U5.7 (EP), U6.2 (ADDR), U6.3 (GND), U7.1 (GND), U7.5 (SDO), U7.7 (GND), U8.2 (GND)

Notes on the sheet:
USB-C input, ESD protection, PTC fuse
5V -> 3V3 buck regulator
ESP32-S3-WROOM-1 (native USB, no UART bridge)
Status LED (WS2812B on ~4.3V) + power-on LED
Sensors: SCD41 CO2/T/RH, SGP41 VOC/NOx, BME280 pressure, BH1750 lux
Test points
DNP expansion footprints (see docs/hardware-expandability.md)
Mounting holes

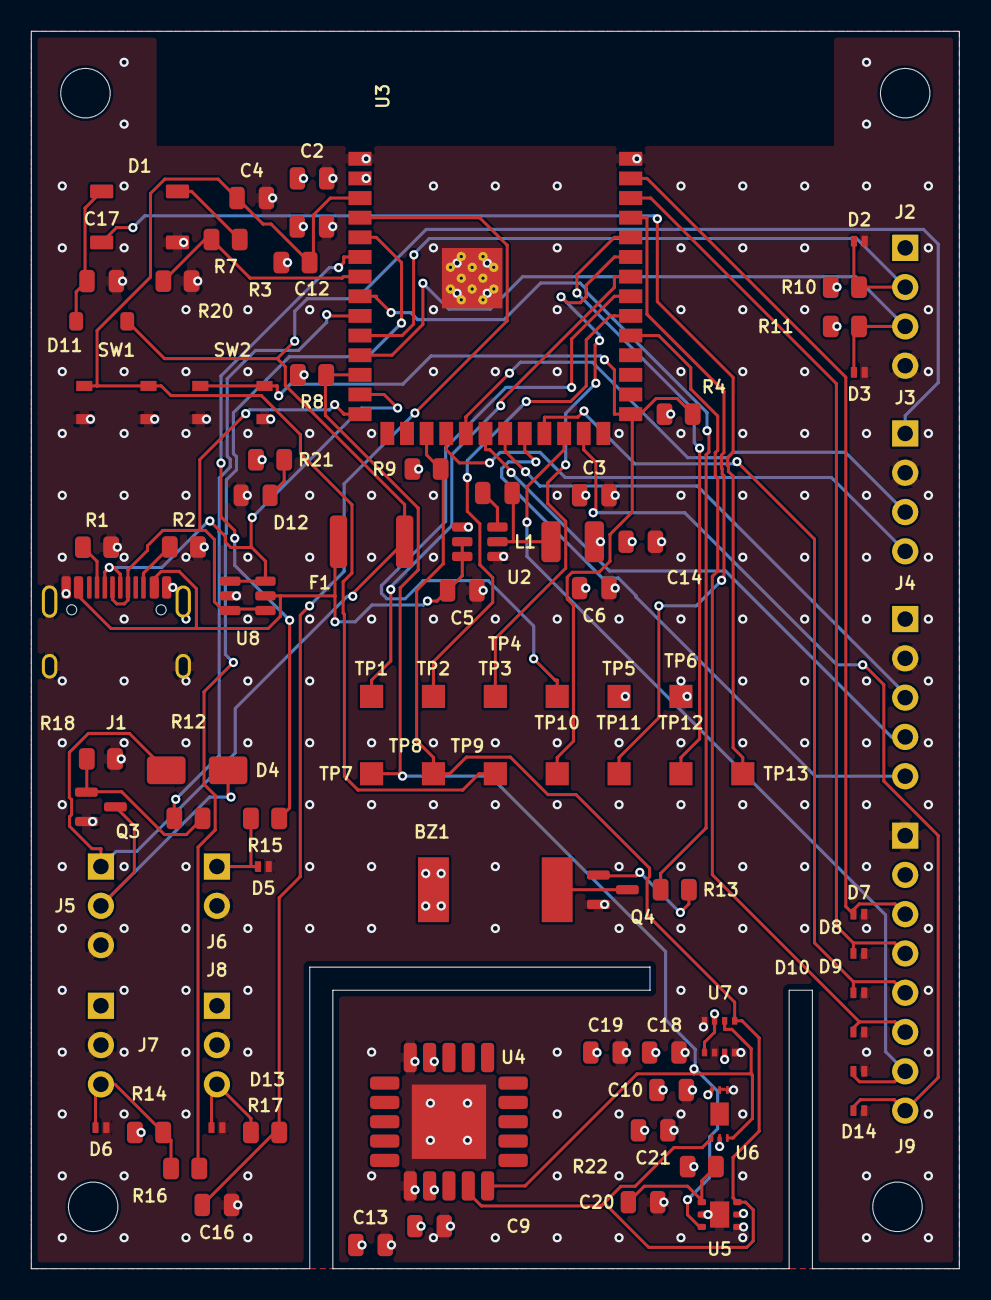
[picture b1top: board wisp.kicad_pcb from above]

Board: 4 copper layers, 60.0 x 80.0 mm, 91 parts (0 on the bottom side), 51 nets.

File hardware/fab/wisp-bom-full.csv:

"Designator","Qty","Value","Footprint","MPN","Manufacturer","Rating","LCSC","DNP"
"BZ1","1","Buzzer","Buzzer_Beeper:Buzzer_CUI_CPT-9019S-SMT","CPT-9019S-SMT","CUI Devices","piezo transducer, external drive","C95163","DNP"
"C16","1","100nF","Capacitor_SMD:C_0805_2012Metric","CL21B104KBCNNNC","Samsung","50V X7R, ADC filter","C1711",""
"C2,C7,C9,C10,C17-C19","7","100nF","Capacitor_SMD:C_0805_2012Metric","CL21B104KBCNNNC","Samsung","50V X7R","C1711",""
"C3,C12,C13","3","10uF","Capacitor_SMD:C_0805_2012Metric","CL21A106KOQNNNE","Samsung","16V X5R","C1713",""
"C4,C20,C21","3","1uF","Capacitor_SMD:C_0805_2012Metric","CL21B105KBFNNNE","Samsung","50V X7R","C28323",""
"C5","1","10uF","Capacitor_SMD:C_0805_2012Metric","CL21A106KOQNNNE","Samsung","25V X5R","C1713",""
"C6,C14","2","22uF","Capacitor_SMD:C_0805_2012Metric","CL21A226MOQNNNE","Samsung","16V X5R","C98190",""
"D1","1","WS2812B","LED_SMD:LED_WS2812B_PLCC4_5.0x5.0mm_P3.2mm","WS2812B-B/T","Worldsemi","VDD 3.5-5.3V","C2761795",""
"D11","1","1N4148W","Diode_SMD:D_SOD-123","1N4148W-7-F","Diodes Incorporated","drops +5V_EXT to ~4.3V for D1","C83528",""
"D12","1","GREEN","LED_SMD:LED_0805_2012Metric","KT-0805G","Hubei KENTO Elec","green, power-on indicator","C2297",""
"D2,D3,D5-D10,D13-D15","11","PESD5V0L1UL","Diode_SMD:D_SOD-882","PESD5V0L1UL","Nexperia","","C552556",""
"D4","1","SS14","Diode_SMD:D_SMA","SS14","MDD (Microdiode Semiconductor)","Schottky 1A/40V, flyback for the switched output","C2480","DNP"
"F1","1","500mA","Fuse:Fuse_1812_4532Metric","MF-MSMF050-2","Bourns","PTC, 500mA hold, 6V","C17313",""
"J1","1","USB-C","Connector_USB:USB_C_Receptacle_HRO_TYPE-C-31-M-12","TYPE-C-31-M-12","HRO","","C165948",""
"J2","1","Second I2C Bus","Connector_PinHeader_2.54mm:PinHeader_1x04_P2.54mm_Vertical","","","","","DNP"
"J3","1","mmWave UART (LD2410)","Connector_PinHeader_2.54mm:PinHeader_1x04_P2.54mm_Vertical","","","","","DNP"
"J4","1","I2S Mic (INMP441)","Connector_PinHeader_2.54mm:PinHeader_1x05_P2.54mm_Vertical","","","","","DNP"
"J5","1","Switched DC Output","Connector_PinHeader_2.54mm:PinHeader_1x03_P2.54mm_Vertical","","","","","DNP"
"J6","1","Reed/Hall Contact","Connector_PinHeader_2.54mm:PinHeader_1x02_P2.54mm_Vertical","","","","","DNP"
"J7","1","1-Wire Bus","Connector_PinHeader_2.54mm:PinHeader_1x03_P2.54mm_Vertical","","","","","DNP"
"J8","1","Analog Sensor Pad","Connector_PinHeader_2.54mm:PinHeader_1x03_P2.54mm_Vertical","","","","","DNP"
"J9","1","Expansion Header","Connector_PinHeader_2.54mm:PinHeader_1x08_P2.54mm_Vertical","","","","","DNP"
"L1","1","2.2uH","Inductor_SMD:L_1210_3225Metric","SRN3015-2R2M","Bourns","Isat >= 1.5A, DCR < 100mOhm","C2041716",""
"Q3","1","AO3400A","Package_TO_SOT_SMD:SOT-23","AO3400A","Alpha & Omega","logic-level N-FET, 5.7A, Vgs(th) < 1.4V","C20917","DNP"
"Q4","1","MMBT3904","Package_TO_SOT_SMD:SOT-23","MMBT3904","onsemi","","C81464","DNP"
"R1,R2","2","5.1k","Resistor_SMD:R_0805_2012Metric","RC0805FR-075K1L","Yageo","1%, 1/8W","C84375",""
"R10,R11","2","4.7k","Resistor_SMD:R_0805_2012Metric","RC0805FR-074K7L","Yageo","1%","C60816","DNP"
"R12","1","100R","Resistor_SMD:R_0805_2012Metric","RC0805FR-07100RL","Yageo","1%, gate series","C105577","DNP"
"R13","1","1k","Resistor_SMD:R_0805_2012Metric","RC0805FR-071KL","Yageo","1%, base series","C95781","DNP"
"R14","1","4.7k","Resistor_SMD:R_0805_2012Metric","RC0805FR-074K7L","Yageo","1%, 1-Wire pull-up","C60816","DNP"
"R15-R17","3","220R","Resistor_SMD:R_0805_2012Metric","RC0805FR-07220RL","Yageo","1%, ESD series","C114519",""
"R18","1","100k","Resistor_SMD:R_0805_2012Metric","RC0805FR-07100KL","Yageo","1%, gate pull-down","C96346","DNP"
"R21","1","2.2k","Resistor_SMD:R_0805_2012Metric","RC0805FR-072K2L","Yageo","1%, 1/8W","C114561",""
"R22","1","4.7R","Resistor_SMD:R_0805_2012Metric","RC0805FR-074R7L","Yageo","1%, SGP41 VDD RC element","C137513",""
"R3,R4,R20","3","10k","Resistor_SMD:R_0805_2012Metric","RC0805FR-0710KL","Yageo","1%, 1/8W","C84376",""
"R7","1","330R","Resistor_SMD:R_0805_2012Metric","RC0805FR-07330RL","Yageo","1%, 1/8W","C105878",""
"R8,R9","2","4.7k","Resistor_SMD:R_0805_2012Metric","RC0805FR-074K7L","Yageo","1%, I2C pull-up","C60816",""
"SW1","1","RESET","Button_Switch_SMD:SW_SPST_PTS810","PTS810 SJM 250 SMTR LFS","C&K","","C116501",""
"SW2","1","BOOT","Button_Switch_SMD:SW_SPST_PTS810","PTS810 SJM 250 SMTR LFS","C&K","","C116501",""
"U2","1","AP63203WU-7","Package_TO_SOT_SMD:TSOT-23-6","AP63203WU-7","Diodes Incorporated","2A sync buck, fixed 3.3V","C780769",""
"U3","1","ESP32-S3-WROOM-1-N8","wisp:ESP32-S3-WROOM-1","ESP32-S3-WROOM-1-N8","Espressif","8MB flash, no PSRAM","C2913198",""
"U4","1","SCD41-D-R2","Sensor:Sensirion_SCD4x-1EP_10.1x10.1mm_P1.25mm_EP4.8x4.8mm","SCD41-D-R2","Sensirion","CO2/T/RH, I2C 0x62","",""
"U5","1","SGP41","wisp:Sensirion_DFN-6-1EP_2.44x2.44mm_P0.8mm_EP1.25x1.7mm","SGP41-D-R4","Sensirion","VOC/NOx, I2C 0x59","",""
"U6","1","BH1750FVI-TR","wisp:BH1750FVI-TR_WSOF6","BH1750FVI-TR","ROHM","lux, I2C 0x23","C78960",""
"U7","1","BME280","Package_LGA:Bosch_LGA-8_2.5x2.5mm_P0.65mm_ClockwisePinNumbering","BME280","Bosch Sensortec","pressure/T/RH, I2C 0x76","C92489",""
"U8","1","USBLC6-2SC6","Package_TO_SOT_SMD:SOT-23-6","USBLC6-2SC6","STMicroelectronics","ESD array, D+/D-/VBUS","C7519",""
